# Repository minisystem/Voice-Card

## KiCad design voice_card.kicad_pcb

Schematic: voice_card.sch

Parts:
C1, C2, C5, C7, C18, C19, C22, C26: 100n; SM0603-C-JRL
C3, C15: 2.2n 1%; SM0805-HAND; Digikey 399-9198-1-ND
C4, C6, C9, C13, C16, C17, C20, C25: 100p; SM0603-C-JRL; Digikey 399-1122-1-ND
C8, C27: 100n**; SM0603-C-JRL
C10, C21: 18p; SM0603-C-JRL; Digikey 399-1112-1-ND
C11, C12, C23, C24, C35, C36, C37, C38, C39, C40: 100n; SM0603-C-JRL; Digikey 478-1395-1-ND
C14, C28: 100p; SM0603-C-JRL
C29, C30, C31, C32: 270pF; SM0603-C-JRL
C33, C34: 47pF; SM0603-C-JRL
D1, D2: BAV70; SOT23-JRL; Digikey BAV70-V-GS08CT-ND
J1: DDR3-DIMM; DDR3-DIMM-MO-269
Q1, Q6: MMBF4391LT1G; SOT23-JRL; Digikey MMBF4391LT1GOSCT-ND
Q2, Q8: 2N3904; SOT23-JRL
Q3, Q7: BCM847; SOT363-JRL; Digikey 568-6098-1-ND
Q4, Q9: DMMT3904; SOT363-JRL
Q5, Q10: DMMT3906; SOT363-JRL
Q11: BC857BS; SOT363-JRL
R1, R5, R24, R61, R68, R78, R97, R109: 100K; SM0603-R-JRL
R2, R18, R29, R38, R48, R60, R69, R80: 10K; SM0603-R-JRL; Digikey P10.0KCCT-ND
R3, R10, R11, R20, R23, R28, R50, R54, R55, R62, R64, R67: 56K; SM0603-R-JRL; Digikey P56.0KCCT-ND
R4, R27, R51, R66: 1M; SM0603-R-JRL; Digikey P1.00MCCT-ND
R6, R52: 680; SM0603-R-JRL; Digikey P680CCT-ND
R7, R12, R14, R70, R72, R73, R98: 10K; SM0603-R-JRL
R8, R71: 22K; SM0603-R-JRL
R9, R53: 39K; SM0603-R-JRL; Digikey P39.0KCCT-ND
R13, R56: 1.5M; SM0603-R-JRL; Digikey P1.50MCCT-ND
R15, R57: 33K; SM0603-R-JRL; Digikey P33.0KCCT-ND
R16, R58: 91K; SM0603-R-JRL; Digikey P91.0KCCT-ND
R17, R22, R26, R59, R63, R65: 15K; SM0603-R-JRL; Digikey P15.0KCCT-ND
R19, R76: 33K; SM0603-R-JRL
R21, R77: 3.3K**; SM0603-R-JRL
R25, R79: 330K; SM0603-R-JRL
R30, R39, R81, R87: 82K*; SM0603-R-JRL
R31, R40, R82, R88, R120: 4.7K; SM0603-R-JRL
R33, R37, R42, R84, R86, R90: 2.2K; SM0603-R-JRL
R34, R43, R85, R91: 270K; SM0603-R-JRL
R35, R74: 3.3K; SM0603-R-JRL; Digikey P3.30KCCT-ND
R36, R75: 20K; SM0603-R-JRL; Digikey P20.0KCCT-ND
R41, R44, R47, R49, R89, R92, R95, R96, R122: 47K; SM0603-R-JRL
R45, R93, R103, R105: 150K; SM0603-R-JRL
R46, R94: 15K; SM0603-R-JRL
R99, R100, R101, R102: 18K; SM0603-R-JRL
R104, R110, R121: 1.5K; SM0603-R-JRL
R106, R107, R108, R115, R116, R117, R118: 68K; SM0603-R-JRL
R111, R112, R113, R114, R123, R124: 560; SM0603-R-JRL
R119: 1K 3300 ppm/K; SM0805-HAND
R125: 1.5M; SM0603-R-JRL
TC1, TC2: 1K 3300ppm/K; SM0805-HAND; Digikey P1.0KCDCT-ND
TP1, TP8: TEST_POINT; TEST_PAD
TP2, TP3, TP4, TP5, TP6, TP7, TP9, TP10, TP11, TP12, TP13, TP14: TEST_POINT; TEST_POINT_5000_SERIES
U1, U2, U8, U11: TL074-; TSSOP-14_4.4x5mm_Pitch0.65mm
U3, U12: NE555; TSSOP8-JRL
U4, U9: LF351; so-8; Digikey CA3140AMZ-ND
U5, U10, U15, U16, U20: TL072-; TSSOP8-JRL
U6, U13: LM311M; TSSOP8-JRL; Digikey 296-1388-1-ND
U7, U14: CD4052; TSSOP-16_4.4x5mm_Pitch0.65mm
U17, U18, U19: LM13700; SO16-JRL

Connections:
+12V: C1.1, C7.1, C11.1, C18.1, C23.1, C26.1, C35.1, C37.1, C39.1, J1.6, J1.12, J1.26, J1.37, J1.52, J1.72, J1.88, J1.97, J1.117, J1.126, J1.132, J1.146, J1.157, J1.172, J1.192, J1.208, J1.217, J1.237, R8.2, R12.1, R13.2, R14.1, R21.2, R36.2, R46.1, R56.2, R71.2, R72.1, R73.1, R75.2, R77.2, R94.1, U1.4 (V+), U2.4 (V+), U3.4 (R), U3.8 (VCC), U4.7 (V+), U5.8 (V+), U6.8 (V+), U7.16 (VDD), U8.4 (V+), U9.7 (V+), U10.8 (V+), U11.4 (V+), U12.4 (R), U12.8 (VCC), U13.8 (V+), U14.16 (VDD), U15.8 (V+), U16.8 (V+), U17.11 (V+), U18.11 (V+), U19.11 (V+), U20.8 (V+)
-12V: C2.2, C12.2, C19.2, C24.2, C36.2, C38.2, C40.2, J1.7, J1.18, J1.29, J1.43, J1.49, J1.64, J1.76, J1.101, J1.127, J1.138, J1.149, J1.163, J1.169, J1.184, J1.196, J1.221, R22.1, R23.1, R25.2, R28.1, R34.1, R43.1, R63.1, R64.1, R67.1, R79.2, R85.1, R91.1, R125.2, U1.11 (V-), U2.11 (V-), U4.4 (V-), U5.4 (V-), U6.1 (GND), U6.4 (V-), U8.11 (V-), U9.4 (V-), U10.4 (V-), U11.11 (V-), U13.1 (GND), U13.4 (V-), U15.4 (V-), U16.4 (V-), U17.6 (V-), U18.6 (V-), U19.6 (V-), U20.4 (V-)
EG1_ATTACK_CV: J1.83, J1.203, R30.1
EG1_DECAY_CV: J1.89, J1.209, U7.1 (Y0)
EG1_ENV_OUT: C8.1, J1.93, J1.213, R5.1, R44.2, U2.7, U3.6 (THR)
EG1_GATE: J1.99, J1.219, R19.2, R24.1
EG1_INV_OUT: J1.90, J1.210, R1.2, U2.8
EG1_RELEASE_CV: J1.92, J1.212, U7.4 (Y3), U7.5 (Y1)
EG1_SUSTAIN_CV: J1.96, J1.216, U7.12 (X0)
EG2_ATTACK_CV: J1.106, J1.226, R81.1
EG2_DECAY_CV: J1.112, J1.232, U14.1 (Y0)
EG2_ENV_OUT: C27.1, J1.116, J1.236, R68.1, R92.2, U11.7, U12.6 (THR)
EG2_GATE: J1.120, J1.240, R76.2, R78.1
EG2_INV_OUT: J1.113, J1.233, R61.2, U11.8
EG2_RELEASE_CV: J1.115, J1.235, U14.4 (Y3), U14.5 (Y1)
EG2_SUSTAIN_CV: J1.119, J1.239, U14.12 (X0)
GND: C1.2, C2.1, C7.2, C11.2, C12.1, C18.2, C19.1, C23.2, C24.1, C26.2, C29.2, C30.2, C31.2, C32.2, C33.2, C35.2, C36.1, C37.2, C38.1, C39.2, C40.1, J1.5, J1.8, J1.10, J1.11, J1.13, J1.14, J1.16, J1.17, J1.19, J1.22, J1.28, J1.30, J1.31, J1.32, J1.33, J1.35, J1.36, J1.38, J1.39, J1.41, J1.44, J1.47, J1.50, J1.51, J1.53, J1.54, J1.55, J1.56, J1.57, J1.59, J1.60, J1.61, J1.62, J1.63, J1.66, J1.67, J1.68, J1.70, J1.71, J1.75, J1.78, J1.79, J1.80, J1.81, J1.82, J1.84, J1.85, J1.86, J1.87, J1.91, J1.94, J1.95, J1.98, J1.100, J1.102, J1.103, J1.104, J1.105, J1.107, J1.108, J1.109, J1.110, J1.111, J1.114, J1.118, J1.125, J1.128, J1.130, J1.131, J1.133, J1.134, J1.136, J1.137, J1.139, J1.142, J1.148, J1.150, J1.151, J1.152, J1.153, J1.155, J1.156, J1.158, J1.159, J1.161, J1.162, J1.164, J1.167, J1.170, J1.171, J1.173, J1.174, J1.175, J1.176, J1.177, J1.179, J1.180, J1.181, J1.182, J1.183, J1.186, J1.187, J1.188, J1.190, J1.191, J1.195, J1.198, J1.199, J1.200, J1.201, J1.202, J1.204, J1.205, J1.206, J1.207, J1.211, J1.214, J1.215, J1.218, J1.220, J1.222, J1.223, J1.224, J1.225, J1.227, J1.228, J1.229, J1.230, J1.231, J1.234, J1.238, Q2.1 (E), Q3.5 (B2), Q4.2, Q5.1, Q7.5 (B2), Q8.1 (E), Q9.2, Q10.1, Q11.2 (B1), R3.2, R7.1, R24.2, R33.1, R35.1, R38.1, R42.1, R47.2, R50.2, R70.1, R74.1, R78.2, R80.1, R84.1, R90.1, R95.2, R98.1, R104.2, R110.1, R111.1, R112.1, R113.1, R114.1, R119.2, R122.2, R123.2, R124.2, TC1.1, TC2.1, U1.3 (+), U1.5 (+), U1.12 (+), U2.3 (+), U2.5 (+), U3.1 (GND), U4.3 (NON), U5.3 (+), U5.5 (+), U7.2 (Y2), U7.6 (Inh), U7.7 (VEE), U7.8 (VSS), U7.11 (X3), U7.14 (X1), U8.3 (+), U8.5 (+), U8.12 (+), U9.3 (NON), U10.3 (+), U10.5 (+), U11.3 (+), U11.5 (+), U12.1 (GND), U14.2 (Y2), U14.6 (Inh), U14.7 (VEE), U14.8 (VSS), U14.11 (X3), U14.14 (X1), U17.3 (+), U17.14 (+), U18.3 (+), U18.14 (+), U20.5 (+)
Iabc: Q11.3 (C2), R99.2, R100.2, R101.2, R102.2
unnamed: C3.1, Q1.2 (S), Q3.3 (C2), U4.2 (INVERTING)
unnamed: C3.2, Q1.1 (D), R6.1
unnamed: C4.1, R15.1, R17.2, R23.2, U1.13 (-)
unnamed: C5.1, Q2.3 (C), R8.1, U7.10 (A)
unnamed: C5.2, R12.2, U3.2 (TR)
unnamed: C6.1, R16.2, R20.1, U5.1
unnamed: C8.2, Q4.3, Q5.3, U2.6 (-)
unnamed: C9.1, Q3.6 (C1), R13.1, U5.6 (-)
unnamed: C9.2, R29.1, U5.7
unnamed: C10.1, R26.1, U6.2 (+)
unnamed: C10.2, Q1.3 (G), R35.2, U6.7
unnamed: C13.2, R36.1, R38.2, U6.3 (-)
unnamed: C14.1, R37.1, U2.1
unnamed: C14.2, Q4.6, Q5.6, R45.1, TP6.1, U2.2 (-)
unnamed: C15.1, Q6.2 (S), Q7.3 (C2), U9.2 (INVERTING)
unnamed: C15.2, Q6.1 (D), R52.1
unnamed: C16.1, R57.1, R59.2, R64.2, U8.13 (-)
unnamed: C17.1, R58.2, R62.1, U10.1
unnamed: C20.1, Q7.6 (C1), R56.1, U10.6 (-)
unnamed: C20.2, R69.1, U10.7
unnamed: C21.1, R65.1, U13.2 (+)
unnamed: C21.2, Q6.3 (G), R74.2, U13.7
unnamed: C22.1, Q8.3 (C), R71.1, U14.10 (A)
unnamed: C22.2, R72.2, U12.2 (TR)
unnamed: C25.2, R75.1, R80.2, U13.3 (-)
unnamed: C27.2, Q9.3, Q10.3, U11.6 (-)
unnamed: C28.1, R86.1, U11.1
unnamed: C28.2, Q9.6, Q10.6, R93.1, TP13.1, U11.2 (-)
unnamed: C29.1, U15.5 (+), U17.5
unnamed: C30.1, U15.3 (+), U17.12
unnamed: C31.1, U16.5 (+), U18.5
unnamed: C32.1, U16.3 (+), U18.12
unnamed: C33.1, R122.1, U19.12, U20.3 (+)
unnamed: C34.1, R121.2, U20.7
unnamed: C34.2, Q11.6 (C1), R125.1, U20.6 (-)
unnamed: D1.2 (A2), R9.2, R10.1, U1.1
unnamed: D1.3 (K), R17.1, R22.2
unnamed: D2.2 (A2), R53.2, R54.1, U8.1
unnamed: D2.3 (K), R59.1, R63.2
unnamed: Q2.2 (B), R19.1, R25.1
unnamed: Q3.1 (E1), Q3.4 (E2), R29.2
unnamed: Q3.2 (B1), R20.2, TC1.2
unnamed: Q4.1, R31.2, R33.2, R34.2, TP3.1
unnamed: Q4.4, Q4.5, Q5.4, Q5.5, R37.2
unnamed: Q5.2, R40.2, R42.2, R43.2, TP5.1
unnamed: Q7.1 (E1), Q7.4 (E2), R69.2
unnamed: Q7.2 (B1), R62.2, TC2.2
unnamed: Q8.2 (B), R76.1, R79.1
unnamed: Q9.1, R82.2, R84.2, R85.2, TP10.1
unnamed: Q10.2, R88.2, R90.2, R91.2, TP12.1
unnamed: Q9.4, Q9.5, Q10.4, Q10.5, R86.2
unnamed: Q11.1 (E1), Q11.4 (E2), R121.1
unnamed: R1.1, R5.2, U2.9 (-)
unnamed: R2.1, R3.1, R4.2, U1.10 (+)
unnamed: R10.2, R11.1, U1.6 (-)
unnamed: R7.2, R14.2, U2.10 (+)
unnamed: R6.2, R18.1, R26.2, TP1.1, U4.6 (OUTPUT)
unnamed: R9.1, R18.2, R27.2, R28.2, U1.2 (-)
unnamed: R21.1, U3.5 (CV)
unnamed: R30.2, R31.1, TP2.1
unnamed: R39.1, U7.3 (Y)
unnamed: R39.2, R40.1, TP4.1
unnamed: R41.1, R45.2, TP7.1, U2.14
unnamed: R41.2, R44.1, U2.13 (-)
unnamed: R46.2, U7.15 (X2)
unnamed: R47.1, R49.2, U2.12 (+)
unnamed: R48.1, R50.1, R51.2, U8.10 (+)
unnamed: R49.1, U7.13 (X)
unnamed: R52.2, R60.1, R65.2, TP8.1, U9.6 (OUTPUT)
unnamed: R53.1, R60.2, R66.2, R67.2, U8.2 (-)
unnamed: R54.2, R55.1, U8.6 (-)
unnamed: R61.1, R68.2, U11.9 (-)
unnamed: R70.2, R73.2, U11.10 (+)
unnamed: R77.1, U12.5 (CV)
unnamed: R81.2, R82.1, TP9.1
unnamed: R87.1, U14.3 (Y)
unnamed: R87.2, R88.1, TP11.1
unnamed: R89.1, R93.2, TP14.1, U11.14
unnamed: R89.2, R92.1, U11.13 (-)
unnamed: R94.2, U14.15 (X2)
unnamed: R95.1, R96.2, U11.12 (+)
unnamed: R96.1, U14.13 (X)
unnamed: R99.1, U17.1
unnamed: R100.1, U17.16
unnamed: R101.1, U18.1
unnamed: R102.1, U18.16
unnamed: R97.1, R98.2, R103.2
unnamed: R97.2, R104.1, U19.3 (+)
unnamed: R105.2, R111.2, R115.2, U17.4 (-), U19.5
unnamed: R106.1, R112.2, R116.2, U17.13 (-)
unnamed: R106.2, R115.1, U15.6 (-), U15.7
unnamed: R107.1, R113.2, R117.2, U18.4 (-)
unnamed: R107.2, R116.1, U15.1, U15.2 (-)
unnamed: R108.1, R114.2, R118.2, U18.13 (-)
unnamed: R108.2, R117.1, U16.6 (-), U16.7
unnamed: R109.1, R110.2, U19.4 (-)
unnamed: R120.1, R124.1, U19.13 (-)
unnamed: R123.1, U19.14 (+)
unnamed: U3.3 (Q), U7.9 (B)
unnamed: U12.3 (Q), U14.9 (B)
RES_CTRL: J1.73, J1.193, U19.1
VCA_CTRL: J1.74, J1.194, U19.16
VCA_IN: J1.69, J1.189, R120.2
VCA_OUT: J1.65, J1.185, U20.1, U20.2 (-)
VCF_CTRL: J1.77, J1.197, Q11.5 (B2), R119.1
VCF_IN: J1.48, J1.168, R103.1, R105.1
VCF_OUT: J1.58, J1.178, R109.2, R118.1, U16.1, U16.2 (-)
VCO1_PITCH_CV: C6.2, J1.20, J1.140, U5.2 (-)
VCO1_PULSE: J1.4, J1.124, R4.1, U1.8
VCO1_PWM_CV: J1.3, J1.123, R2.2
VCO1_SAW: D1.1 (A1), J1.2, J1.122, R11.2, U1.7, U1.9 (-)
VCO1_SCALE: J1.15, J1.135, R16.1
VCO1_SYNC_IN: C13.1, J1.21, J1.141
VCO1_TRI: C4.2, J1.9, J1.129, R15.2, U1.14
VCO1_TRI_SHAPE: J1.1, J1.121, R27.1
VCO2_PITCH_CV: C17.2, J1.45, J1.165, U10.2 (-)
VCO2_PULSE: J1.25, J1.145, R51.1, U8.8
VCO2_PWM_CV: J1.27, J1.147, R48.2
VCO2_SAW: D2.1 (A1), J1.24, J1.144, R55.2, U8.7, U8.9 (-)
VCO2_SCALE: J1.40, J1.160, R58.1
VCO2_SYNC_IN: C25.1, J1.46, J1.166
VCO2_TRI: C16.2, J1.34, J1.154, R57.2, U8.14
VCO2_TRI_SHAPE: J1.23, J1.143, R66.1

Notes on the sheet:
VCO1 RAMP
VCO2 RAMP
LM13700 Darlington pair buffers not used
VCA
VCF Exponential converter
1μ DC blocking cap and 100K resistor (for 10Vp-p input) needed before VCA input stage. VCA offset adjust also needed. See Juno 106 and Jupiter 8 schematics.
**adust R to get threshold of 10V
* ADJUST R7/R8 with T1/T2 to get 20-25 s max A/D/R
**match C5 value between ADSR modules. 95nF gives min attack of <1.5ms
0-10V CV
+5V
VC ADSR
original design by Massimo Ischia http://digilander.libero.it/ismsynth/vc-adsr-1.2.jpg adapted for 0-10V input and 0-10V output

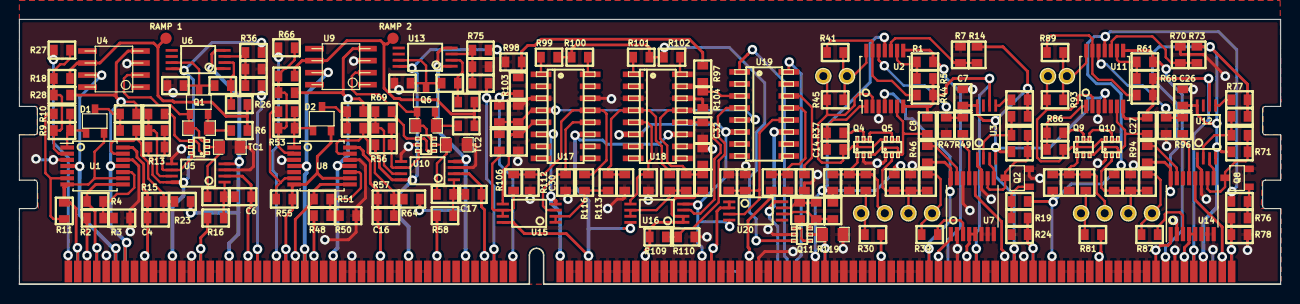
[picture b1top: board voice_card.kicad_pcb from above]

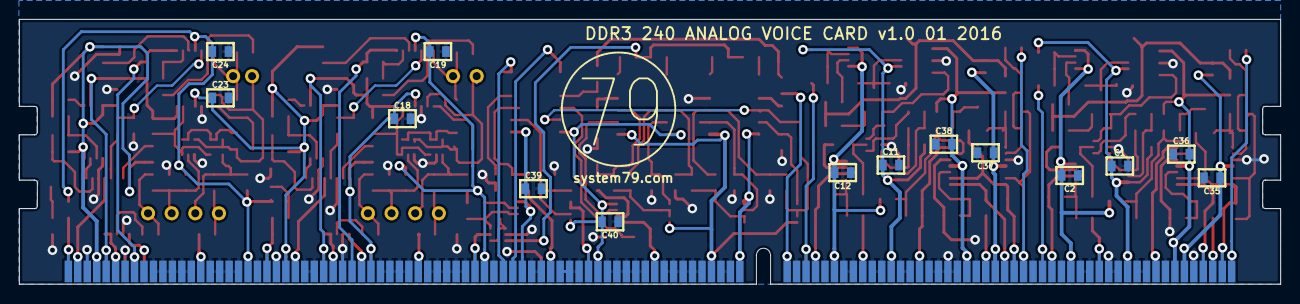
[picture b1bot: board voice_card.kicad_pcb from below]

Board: 2 copper layers, 133.3 x 28.0 mm, 214 parts (15 on the bottom side), 141 nets.

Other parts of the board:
system79-logo-12mm: VAL**; system79-logo-12mm

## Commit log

2015-11-19 VCO1 and VCO2 done in schematic. Need to check
2015-11-19 added VCA and VCF to voice card schematic. added .gitignore
2015-11-19 2VCOs, 1VCF, 1VCA, 2EGs now in schematic
2015-11-20 added 2x60 120 pin PCI connector to schematic
2015-11-20 annotated schematic, starting assigning footprints
2015-11-20 fiddling with PCI card edge module. Not sure it's right yet
2015-11-21 laying out and routing VCO1 core
2015-11-21 starting to layout waveshapers for VCO1
2015-11-21 VCO1 more or less routed
2015-11-21 VCO1 basically routed. bringing in and output pins to PCI connector. Need to swap pins to get pinout order correct
2015-11-21 starting to place VCO2 components
2015-11-22 VCO1 and VCO2 rough layout done. Starting to place VCF and VCA components
2015-11-23 routing vcf almost done, then need to do VCA and expo converter
2015-11-23 finishing up VCF/VCA layout and routing
2015-11-23 still working on vcf/vca. getting there
2015-11-24 struggling with EG component layout and routing. Thinking of replacing U2 (TL074) with two TL072s for ease of compact layout
2015-11-24 EG1 routed, just flipping and fitting now
2015-11-24 EG1 routed, some adjustments made to increase compactness
2015-11-24 EG1 done, about to place EG2 components
2015-11-24 starting to place components for EG2
2015-11-25 EG2 placed and routed
2015-11-25 all modules routed for signals, still need to route power. going to branch and try to fit into 133 mm DIMM
2015-11-25 squishing things a little bit more. Need to squeeze it all into 133.35 mm with 3 mm bufferes on each end
2015-11-26 more squishing into 133.35 mm x 30 mm DDR3 DIMM footprint
2015-11-26 using DDR3 DIMM 133.35 x 30.0 mm PCB outline now
2015-11-26 using DDR DIMM MO-269 board outline. working on 240 pin DIMM module
2015-11-27 DDR3 DIMM schematic symbol created, now assigning ins and outs to DIMM pins. Tedious
2015-11-27 DDR3 DIMM connector switched over from PCI in board and schematic. Routing power traces now
2015-11-27 power routed, now stitching grounds
2015-11-28 stitching ground plane
2015-11-28 decoupling caps placed and routed. Still stitching ground plane
2015-11-28 placed silkscreen component references. still need to finish up ground stitching
2015-11-29 stitching done. 21 unconnected, all of which should be resolved by connecting pins on J1
2015-12-08 made connections on DIMM socket bilaterally symmetrical and started to route accordingly
2015-12-08 DIMM connector rewired and rerouted. Need to do another node by node check for connections
2015-12-08 connections look good. one final check and should be ready to order
2015-12-21 added one via to stitch ground. Now just power rails remain unconnected, but each rail is connected for every submodule
2016-01-24 little bit of silkscreen adjustment. Ready to export gerbers and order
2016-01-24 gerbers plotted, ready to order
2016-01-24 ordered from Seeed Studio January 24. Modified DDR3 DIMM edge connector as there was a problem with no solder mask on the bottom side
